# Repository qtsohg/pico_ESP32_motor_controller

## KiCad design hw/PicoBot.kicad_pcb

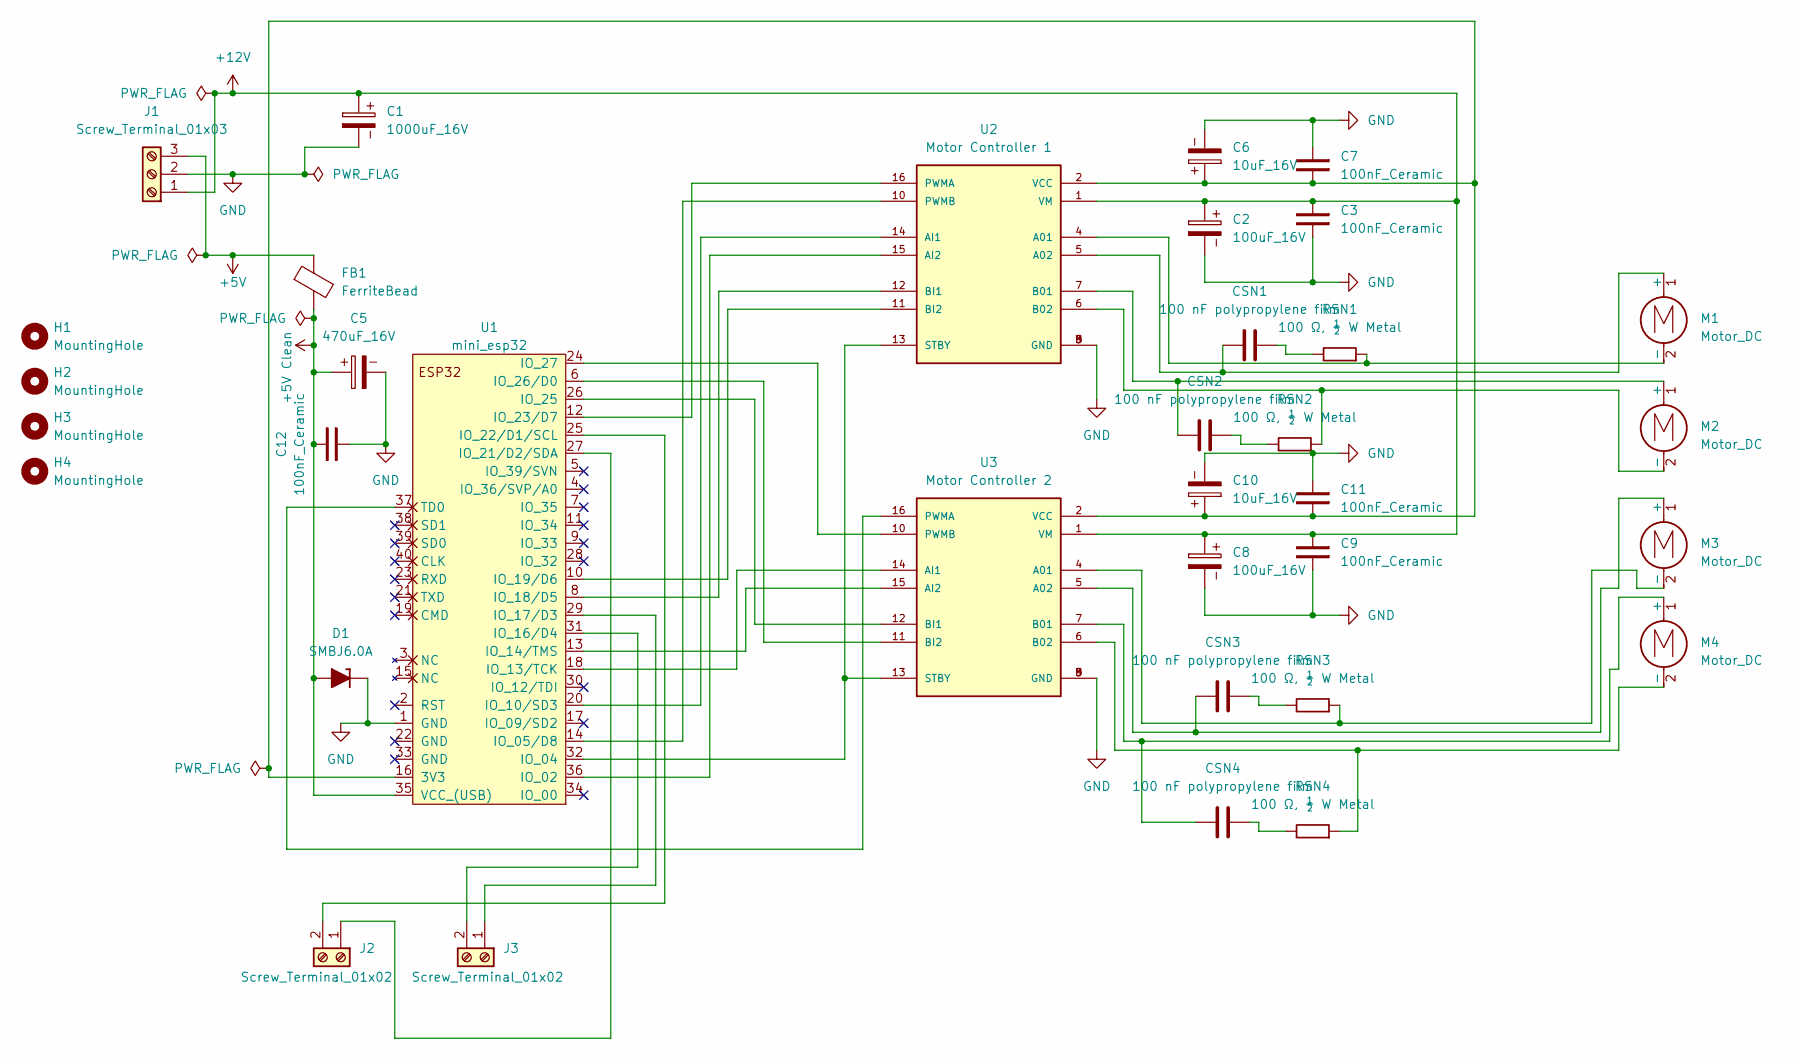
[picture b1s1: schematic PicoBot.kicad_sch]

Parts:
C1: 1000uF_16V; CP_Radial_D10.0mm_P5.00mm
C2, C8: 100uF_16V; CP_Radial_D5.0mm_P2.00mm
C3, C7, C9, C11, C12: 100nF_Ceramic; C_Disc_D5.0mm_W2.5mm_P2.50mm
C5: 470uF_16V; CP_Radial_D8.0mm_P3.50mm
C6, C10: 10uF_16V; CP_Radial_D5.0mm_P2.00mm
CSN1, CSN2, CSN3, CSN4: 100 nF polypropylene film; C_Rect_L7.0mm_W6.0mm_P5.00mm
D1: SMBJ6.0A; D_SMB
FB1: FerriteBead; L_1206_3216Metric
H1, H2, H3, H4: MountingHole; MountingHole_3.2mm_M3
J1: Screw_Terminal_01x03; TerminalBlock_Altech_AK300-3_P5.00mm
J2, J3: Screw_Terminal_01x02; TerminalBlock_Altech_AK300-2_P5.00mm
M1, M2, M3, M4: Motor_DC; TerminalBlock_Altech_AK300-2_P5.00mm
RSN1, RSN2, RSN3, RSN4: 100 Ω, ½ W Metal; R_Axial_DIN0309_L9.0mm_D3.2mm_P15.24mm_Horizontal
U1: mini_esp32; ESP32_mini
U2: Motor Controller 1; MODULE_ROB-14450; PARTREV 11-13-17
U3: Motor Controller 2; MODULE_ROB-14450; PARTREV 11-13-17

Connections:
+5V: FB1.1, J1.3
+5V Clean: C5.1, C12.1, D1.2 (A), FB1.2, U1.35 (VCC_(USB))
+12V: C1.1, C2.1, C3.1, C8.1, C9.1, J1.1, U2.1 (VM), U3.1 (VM)
GND: C1.2, C2.2, C3.2, C5.2, C6.2, C7.1, C8.2, C9.2, C10.2, C11.1, C12.2, D1.1 (K), J1.2, U1.1 (GND), U2.3 (GND), U2.8 (GND), U2.9 (GND), U3.3 (GND), U3.8 (GND), U3.9 (GND)
unnamed: CSN1.2, RSN1.2
unnamed: CSN2.2, RSN2.2
unnamed: CSN3.2, RSN3.2
unnamed: CSN4.2, RSN4.2
unnamed: J2.1, U1.27 (IO_21/D2/SDA)
unnamed: J2.2, U1.25 (IO_22/D1/SCL)
unnamed: J3.1, U1.29 (IO_17/D3)
unnamed: J3.2, U1.31 (IO_16/D4)
unnamed: CSN1.1, M1.1 (+), U2.5 (A02)
unnamed: M1.2 (-), RSN1.1, U2.4 (A01)
unnamed: CSN2.1, M2.1 (+), U2.7 (B01)
unnamed: M2.2 (-), RSN2.1, U2.6 (B02)
unnamed: CSN3.1, M3.1 (+), U3.5 (A02)
unnamed: M3.2 (-), RSN3.1, U3.4 (A01)
unnamed: CSN4.1, M4.1 (+), U3.7 (B01)
unnamed: M4.2 (-), RSN4.1, U3.6 (B02)
unnamed: C6.1, C7.2, C10.1, C11.2, U1.16 (3V3), U2.2 (VCC), U3.2 (VCC)
unnamed: U1.36 (IO_02), U2.15 (AI2)
unnamed: U1.32 (IO_04), U2.13 (STBY), U3.13 (STBY)
unnamed: U1.14 (IO_05/D8), U2.10 (PWMB)
unnamed: U1.20 (IO_10/SD3), U2.14 (AI1)
unnamed: U1.18 (IO_13/TCK), U3.14 (AI1)
unnamed: U1.13 (IO_14/TMS), U3.15 (AI2)
unnamed: U1.8 (IO_18/D5), U2.12 (BI1)
unnamed: U1.10 (IO_19/D6), U2.11 (BI2)
unnamed: U1.12 (IO_23/D7), U2.16 (PWMA)
unnamed: U1.26 (IO_25), U3.12 (BI1)
unnamed: U1.6 (IO_26/D0), U3.11 (BI2)
unnamed: U1.24 (IO_27), U3.10 (PWMB)
unnamed: U1.37 (TD0), U3.16 (PWMA)

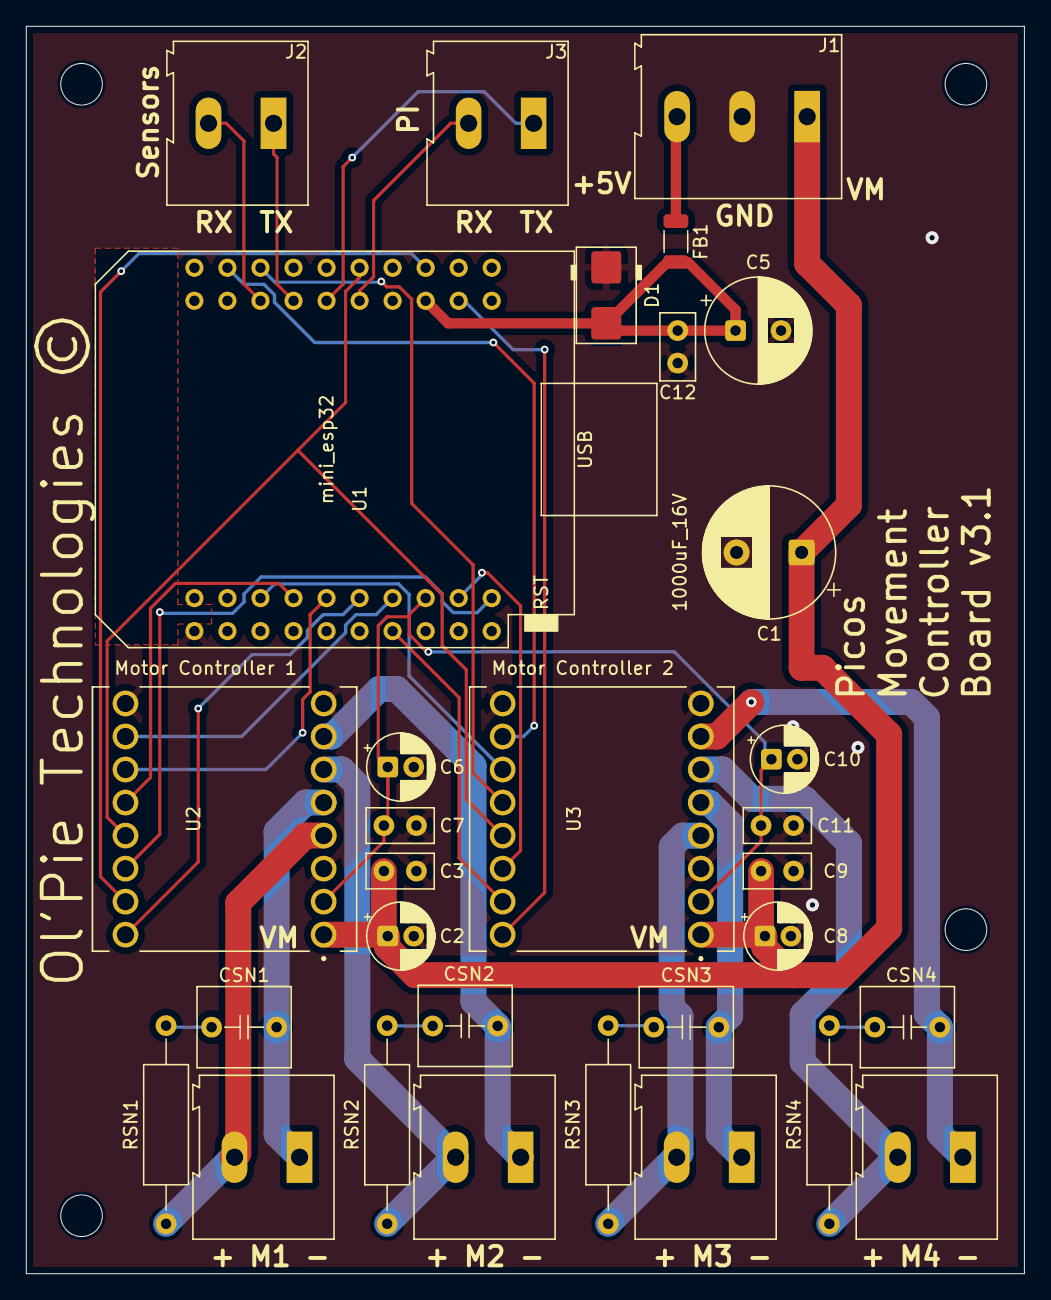
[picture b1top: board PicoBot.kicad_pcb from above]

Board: 2 copper layers, 76.7 x 95.9 mm, 35 parts (0 on the bottom side), 34 nets.

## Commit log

2025-11-05 Initial commit with submodule and original pico board design
2025-11-05 Updated the libs submodule
2025-11-05 chore(libs): register shared libraries (auto-generated)
2025-11-05 Added .gitignore
